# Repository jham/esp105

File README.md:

# esp105 — ESP32-C6 adapter for Mitsubishi CN105

A small board that plugs into the CN105 port of a Mitsubishi mini-split, is powered by it, and
talks to it over its serial port with an ESP32-C6 (Wi-Fi or Thread).

| Folder | Contents |
|---|---|
| [`hardware/`](hardware/) | KiCad 10 project: schematic, routed 2-layer PCB, project libraries, BOM with verified LCSC numbers, and the guide for working on it. Start with [hardware/README.md](hardware/README.md). |
| [`software/`](software/) | Firmware for the board, two choices: ESPHome over Wi-Fi for Home Assistant, or Matter over Thread for any Matter controller. Build and flashing steps are in `software/wifi/` and `software/matter/`. Start with [software/README.md](software/README.md). |

Open the board in KiCad via `hardware/cn105.kicad_pro`.

## License

The hardware design in [`hardware/`](hardware/) is licensed under the CERN Open Hardware Licence
Version 2 - Permissive; see [hardware/LICENSE](hardware/LICENSE). The firmware in
[`software/`](software/) is licensed under the Apache License 2.0; see
[software/LICENSE](software/LICENSE).

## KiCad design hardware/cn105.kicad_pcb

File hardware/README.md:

# CN105 ↔ ESP32-C6 adapter — hardware

A small board that plugs into the CN105 port of a Mitsubishi mini-split, is powered by it, and talks
to it over its 5 V serial port using an ESP32-C6 module (Wi-Fi or Thread, chosen in firmware).

**Design state:** schematic and board complete at version 0.4.0, not yet ordered (see the title
block, the `ESP105 v…` silkscreen, and [ORDER_LOG.md](ORDER_LOG.md) for what has been built; the
latest boards made are 0.3.0). What changed since 0.3.0 is under
[Changes from 0.3.0 to 0.4.0](#changes-from-030-to-040). ERC 0, DRC 0 errors, schematic parity 0. Board 41.8 × 37.6 mm, 2 layers, ESP32-C6-WROOM-1-N8 with its antenna
overhanging the top edge, Grove socket for the CN105 cable and USB-C both on the bottom edge, four M2.5 holes. The
LCSC numbers in the BOM were checked against JLCPCB's parts database. Board versions are semver;
the git tag is `v<version>` (the early tags `v0.1` and `v0.2` mean 0.1.0 and 0.2.0). A version is
tagged when it is set, whether or not it has been ordered.

## What is in this folder

| File | What it is |
|---|---|
| `cn105.kicad_pro` | The project. Double-click this to open KiCad. Contains JLCPCB-friendly design rules and two net classes (Default 0.25 mm tracks, Power 0.5 mm). |
| `cn105.kicad_sch` | The schematic. Complete, ERC 0. Its title block carries the board version and date. |
| `cn105.kicad_pcb` | The board: 41.8 × 37.6 mm, 2 layers, fully routed, GND pours on both layers. DRC 0 errors. Its title block rev/date feed the `ESP105 v${REVISION}` and `${ISSUE_DATE}` silkscreen texts on the back. |
| `cn105.kicad_sym`, `sym-lib-table` | Project symbol library: the ESP32-C6-WROOM-1 symbol (KiCad 10 does not ship one), derived from the MINI-1 symbol with the WROOM pin numbers. |
| `cn105.pretty/`, `fp-lib-table` | Project footprint library: the Grove HY2.0-4P right-angle SMD socket (drawn from the Megastar ZX-HY2.0-4PWT drawing), Espressif's official ESP32-C6-WROOM-1 footprint, and project copies of the HRO USB-C and TS-1187A switch footprints with working 3D models. The JST PA header footprints (CN105 header through 0.2.0) and the ESP32-C6-MINI-1 footprint from 0.1.0 are kept for reference. Don't delete `fp-lib-table`. |
| `cn105.3dshapes/` | 3D models not shipped with KiCad: Espressif's `ESP32-C6-WROOM-1.step` (and the 0.1.0 `ESP32-C6-MINI-1.step`) and plain-box placeholders for the Grove socket and the JST PA headers (from `tools/models.py`). The USB-C uses KiCad's GCT USB4105 model and the switches KiCad's Alps SKRK model, both near-identical parts. |
| `BOM.csv` | Human-readable parts list with LCSC numbers and the reason for each part. The JLCPCB-format BOM is generated, see below. |
| `cn105-board-3d.png` | Render of the board, regenerated with `kicad-cli pcb render` after board changes. |
| `ORDER_LOG.md` | One entry per board order: version, date, tag, fab and assembly options, what changed. |
| `tools/` | `export_jlcpcb.sh` (+ `export_jlcpcb.py`) writes the JLCPCB order files into `production/`; `set_version.py` records a board version and date in both title blocks; `jlc_stock.py` checks a JLCPCB BOM for stock and Standard-only parts; `silk_values.py` switches footprints to print their Value on the silkscreen. `gen.py`, `ksym.py`, `place.py`, `fp.py`, `models.py`, `module_fp.py` generated the original 0.1.0 starter files and **overwrite everything**; see the last section. |

## How the circuit works (read this with the schematic open)

**CN105 interface.** The board carries a 4-pin Grove (HY2.0) socket, reference CN105, and connects
to the heat pump's CN105 port with a CN105-to-Grove cable wired as on
[serin-labs.com/wiring.html](https://serin-labs.com/wiring.html): JST PAP-05V-S on the heat pump
end, Grove HY2.0-4P on ours, four conductors, the 12 V position left empty.

| Grove pin | Wire | CN105 pin | Signal | Used for |
|---|---|---|---|---|
| 1 | black | 2 | GND | Ground |
| 2 | red | 3 | 5 V | Powers the whole board |
| 3 | white | 4 | TX from the heat pump (5 V logic) | Goes through R2/R3 (10k/15k), which divides 5 V to 3.0 V, then into ESP IO7 (UART RX) |
| 4 | yellow | 5 | RX into the heat pump | Driven by U3, a 74AHCT1G125 buffer powered from 5 V, through R13 (100 Ω), so the heat pump gets a real 5 V signal. U3's input is ESP IO6 (UART TX). R6 holds that line high while the ESP is still booting so the heat pump never sees garbage. |

D4, a dual TVS diode at the socket, clamps ESD on pins 3 and 4. The cable is wired straight
through, pin for pin; the UART crossover (heat pump TX into ESP RX
and back) is built into the numbering. Grove pin 1 is at the end marked "1" on the silkscreen,
the left end when you look into the socket opening from the board edge with the latch window up.
CN105 pin 1 (12 V) stays unconnected in the cable. Verify the CN105 pinout on **your** unit with a
meter before plugging anything in.

**ESP32-C6 module.** U1 (ESP32-C6-WROOM-1-N8, 8 MB flash) with its decoupling C4 (22 µF) and C5
(100 nF) at the 3V3 pin, the EN reset circuit (R1, C1, button RESET), the BOOT button on IO9, and
three 0805 status LEDs: green PWR (R7 1k, IO23, net LED_PWR), red HEAT (R8 330 Ω, IO22, net
LED_HEAT) and blue COOL (R9 330 Ω, IO21, net LED_COOL). The resistor values give the three LEDs
similar brightness at 3.3 V (green about 50 mcd, red and blue 25–30 mcd); green and red are JLCPCB
basic parts, the blue is extended because JLCPCB stocks no basic blue 0805. UART1 is on IO6/IO7 for
the heat pump. UART0 goes to J1, a 3-pin header on the back that is not fitted (TX, RX, GND, for a
3.3 V USB-serial adapter); the console is the module's USB-Serial-JTAG over the USB-C port.
Of the strapping pins, IO9 is the BOOT button and both IO9 and IO8 carry 10k pull-ups (R12, R11) so
boot mode never depends on the weak internal pull-ups; the rest are left unconnected. The LEDs,
buttons, USB-C and module print their Value (PWR, HEAT, COOL, RESET, BOOT, USBC, ESP32-C6) on the
silkscreen instead of their reference designator.

**USB-C.** Wired for USB 2.0 only: D+/D- go straight to the C6's native USB pins (IO13/IO12, module
pads 14/13), so no USB-UART chip is needed. The receptacle's two D+ pads and two D- pads are
bridged on the board, as the USB-C spec requires. R4/R5 (5.1k) on CC1/CC2 tell a USB-C charger or
laptop we want 5 V. U4 (SRV05-4, a 4-channel TVS array with pins 1+6 and 3+4 paired on the board)
clamps ESD on D+, D- and VBUS, since the port lives in a damp metal box and gets plugged into by
hand. The VBUS pins are net `5V_USB_IN`; F1, a resettable fuse, feeds `5V_USB` from it.

**Power.** Two 5 V sources feed the `+5V` rail. USB comes in through F1 and then D1, a Schottky. The heat
pump's 5 V comes in through Q1, a P-channel MOSFET: with no USB present R10 holds its gate low and
it conducts with about 30 mV of drop; plugging in USB pulls the gate high through the `5V_USB`
line and switches it off, so USB can never back-feed the heat pump and the heat pump never drives
the USB port. Q1's body diode still lets the heat pump help out if USB sags. D1 is what keeps the
USB line separate from the rail so the gate reads "USB present". D3 (SMAJ5.0A TVS) sits across the
CN105 5 V input, C7 (100 µF) is the bulk reservoir for Wi-Fi transmit peaks, and U2 (AP2112K-3.3,
600 mA) makes 3.3 V with C2/C3 (10 µF) on its input and output. The PWR_FLAG symbols are not real
parts: they tell KiCad's checker that those nets are powered.

## Working on it in KiCad 10

**Opening.** Double-click `cn105.kicad_pro`. The project carries its own symbol and footprint
library tables, so no library setup is needed. Open the Schematic Editor or PCB Editor from the
project manager; `Home` fits the sheet or board in the window. The board sits at x=100, y=100 mm
on the sheet, so if the PCB editor looks empty press `Home`.

**Schematic.** Hover a wire and press `` ` `` (backtick) to highlight its net; `E` opens any item's
properties; `V` edits a value. **Inspect → Electrical Rules Checker → Run ERC** should report 0.
Parts carry `LCSC` and `MPN` fields; the JLCPCB export reads `LCSC`, and `MPN` is for people.

**From schematic to board.** After any schematic change press `F8` in the PCB editor (Update PCB
from Schematic) to push new parts, values and fields onto the board, then place and route what is
new. The board's `Value` field is what prints on the silkscreen for the LEDs, buttons, connectors
and module, so keep those values short.

**Board basics.** Layers tab on the right: `F.Cu`/`B.Cu` copper, `F.SilkS`/`B.SilkS` printing,
`Edge.Cuts` outline, `F.CrtYd` courtyards (the no-overlap zone around each part). White ratsnest
lines are connections not yet routed. `M` moves, `R` rotates, `E` edits, `X` routes a track, `V`
drops a via while routing, `B` refills the ground pours, `Esc` cancels. Hold `Ctrl` while moving to
ignore the grid. Don't press `F` on a part: that flips it to the back and single-sided assembly is
cheaper. `Ctrl+Shift+M` measures; `Space` sets a local origin so the status bar shows distances
from it.

**Rules already set** (File → Board Setup): 0.2 mm clearance, 0.15 mm minimum track, 0.5 mm vias
with 0.3 mm holes, matching JLCPCB's cheap 2-layer process. Net class `Power` covers `+5V`,
`+3V3`, `GND`, `5V_USB`, `5V_USB_IN` and `5V_CN105` and makes those tracks 0.5 mm
automatically; everything else is 0.25 mm.

**Antenna keep-out.** The 6 mm antenna section of the WROOM-1 (the end away from the pins) hangs
over the top edge. No copper, tracks, vias or parts under it on either layer, and Espressif asks
for no metal, including the enclosure, within about 15 mm of that end.

**Placement rules that matter.** C5 and C6 (100 nF) stay tight against the module 3V3 pin and
U3's VCC pin; C2/C3 at U2; C1, C4 and C7 are relaxed. D3 goes next to the Grove socket with a
short ground return. D1 and R10 can sit anywhere on their nets. The USB D+/D- pair runs side by
side; a via or two and a few millimetres of length mismatch are fine at USB full speed. Both
connectors are placed so their openings are flush with the bottom board edge: the Grove footprint
origin is the centre of its pad pattern (JLCPCB's reference point for the part, 3.85 mm in front
of the pin row) and the housing front is 5.45 mm from it (anchor pads stop at 5.15 mm so they keep
the 0.3 mm copper-to-edge clearance with a flush face), the USB-C origin is JLCPCB's reference point for the part (1.57 mm behind the shell centre) and
the shell front is 5.22 mm from it.

**Footprint origins must match JLCPCB's.** JLC places a part at the origin of *its* footprint
(EasyEDA's), which is the centre of the pad pattern for connectors. The CPL reports our footprint
origin, so a project footprint with its origin elsewhere is placed wrong by that offset; the Grove
socket and the USB-C both had this before 2026-11-23. Check a new footprint against
`https://easyeda.com/api/products/<LCSC>/components?version=6.5.42` (pad coordinates relative to
the origin, units of 10 mil) before trusting the placement preview.

**Checks.** `Inspect → Design Rules Checker` with schematic parity on. Expect 0 errors, 0
unconnected, and four `silk_edge_clearance` warnings where the connector and antenna outlines cross
the board edge. A "thermal relief connection incomplete" error means a GND pad is boxed in by
tracks: draw a short GND track from the pad to the nearest GND via. From the shell:

```bash
/Applications/KiCad/KiCad.app/Contents/MacOS/kicad-cli sch erc --severity-all cn105.kicad_sch
```

```bash
/Applications/KiCad/KiCad.app/Contents/MacOS/kicad-cli pcb drc --severity-all --schematic-parity --refill-zones cn105.kicad_pcb
```

**Version and date.** Both title blocks hold the board version (semver) and the date it was
set; `python3 tools/set_version.py 0.4.0` sets them with the schematic and PCB editors closed, and
the back silkscreen prints them through `${REVISION}` and `${ISSUE_DATE}`. Setting a version and
ordering boards are separate steps, each with a Claude Code skill in `.claude/skills/`:

- `/bump-version` checks whether the design files changed since the last version tag, proposes
  the next version (PATCH for part or export fixes with the schematic and copper unchanged, MINOR
  for schematic or copper changes, MAJOR on request), sets the title blocks, adds a "Changes from
  … to …" section below, runs the checks, commits and tags `v<version>`.
- `/order` builds a tagged version. If the design changed since the last tag it runs
  `/bump-version` first; if not, it orders the last tagged version again without a new number.
  It then exports the order files, waits for you to place the order, logs it in `ORDER_LOG.md`
  and pushes.

## Production files (JLCPCB)

```bash
sh tools/export_jlcpcb.sh
```

Needs KiCad in /Applications. It writes `production/` (git-ignored): `cn105-gerbers.zip` (Gerbers
for F.Cu, B.Cu, both masks, both silkscreens, F.Paste, Edge.Cuts, plus Excellon PTH/NPTH drills),
`cn105-bom-jlcpcb.csv` and `cn105-cpl-jlcpcb.csv` in JLC's column format, built from the `LCSC`
field on every part. The BOM's Comment column is the LCSC code, so JLC's matcher cannot confuse a
part with a similarly named one. Mounting holes are skipped. Through-hole parts are reported at the
centre of their pin pattern, which is what JLC's preview expects (the 0.2.0 CN105 header needed
this; the Grove socket is SMD).

```bash
python3 tools/jlc_stock.py production/cn105-bom-jlcpcb.csv
```

checks every line against JLCPCB's database and flags missing or out-of-stock parts, parts that
force Standard assembly, and which extended parts carry a loading fee.

## Firmware

Two firmwares live in [`../software/`](../software/): ESPHome over Wi-Fi in `software/wifi/` and
Matter over Thread in `software/matter/`, each with build and flashing steps. The pins both rely
on: UART TX GPIO6 and RX GPIO7, LEDs PWR GPIO23 / HEAT GPIO22 / COOL GPIO21 (high is
on), BOOT on GPIO9, console on the USB-C port.

## Bring-up checklist

1. Power from USB only. Measure +3V3 on C3: expect 3.25–3.35 V. The module should enumerate as a
   USB serial/JTAG device on the Mac (`ls /dev/cu.usb*`).
2. Flash the firmware from `software/`. The PWR LED blinks until Wi-Fi joins, then stays on.
3. Measure Grove pin 4 relative to pin 1: ~5 V (USB-powered it'll read ~4.6 V). That's UART idle.
4. Check the cable's orientation. Unplug USB, plug the Serin cable into the board's Grove socket
   with its CN105 end loose, and use the meter's continuity mode, poking a probe (or a bit of wire)
   into the cavities of the CN105 plug. Cavity 1 (the ▲ end) is empty.
   - Cavity 2 (black) beeps to the USB-C shell, which is GND.
   - Cavity 3 (red) beeps to Q1 pin 3, the lone pin on one side of the SOT-23 (the `5V_CN105`
     net), and does **not** beep to the USB-C shell.

   If black does not reach GND, the socket's pin 1 is mirrored relative to the cable; do not
   connect it to the heat pump (see the Grove note under "Things I assumed").
5. Only now plug into the heat pump. Confirm pin 3 is 5 V and pin 2 is ground **with the cable
   unplugged from the board** first, meter on the heat pump side.
6. **Do not have USB and the heat pump connected at the same time** unless the USB host is
   battery powered or you use a USB isolator. USB ties the heat pump's control ground to the
   PC's earth through this board, and the two are not guaranteed to agree. Flash on the bench,
   then install; use OTA afterwards.

## Changes from 0.3.0 to 0.4.0

0.4.0 is laid out and passes ERC, DRC and schematic parity, but it has not been ordered. The 0.3.0
boards (tag `v0.3.0`) have none of these changes, and none of them is needed for 0.3.0 to work.
The board outline, mounting holes, connectors, module position and design rules are unchanged.

### Circuit

- **R13, 100 Ω in series with U3's output** (0603, UNI-ROYAL 0603WAF1000T5E, LCSC C22775, JLCPCB
  basic). U3 pin 4 is now net `CN105_RX_BUF`, and R13 joins it to `CN105_RX_5V` at Grove pin 4.
  The 74AHCT1G125 is only rated for about 2 kV human-body ESD; R13 limits current into it from a
  static discharge, a short or a miswired cable, and costs nothing at 2400 baud.
- **D4, ESD5V0AP dual TVS on Grove pins 3 and 4** (SOT-23, ElecSuper ESD5V0AP, LCSC C5199224,
  extended). Pins 1 and 2 go to `CN105_TX_5V` and `CN105_RX_5V`, pin 3 (the common anode) to GND.
  5 V working voltage, 6 V breakdown, ±30 kV contact; the 3.3 V diodes the M5Stack NanoC6 uses
  would conduct on our 5 V signals.
- **J1, UART0 header, not fitted** (`PinHeader_1x03_P2.54mm_Vertical`, marked DNP so JLCPCB leaves
  it empty): pin 1 TXD0 (module pad 25, GPIO16, net `UART0_TX`), pin 2 RXD0 (pad 24, GPIO17,
  `UART0_RX`), pin 3 GND. With a 3.3 V USB-serial adapter it gives the ROM boot messages, and
  serial flashing with BOOT held, if firmware breaks USB-Serial-JTAG or the USB-C connector is
  damaged. It does not get around the ground warning in step 6 of the bring-up checklist, since a
  USB-serial adapter ties the grounds together just as USB-C does.
- **F1, resettable fuse on USB VBUS** (0805, BHFUSE BSMD0805-075-6V, LCSC C883110, extended; 6 V,
  0.75 A hold, 1.5 A trip). The USB-C VBUS pins and U4's VBUS clamp are now net `5V_USB_IN`
  (renamed from `USBC_5V`, and in the `Power` net class), and F1 feeds `5V_USB` from it. It
  protects the computer's USB port from a fault on this board, such as a solder bridge or a failed
  TVS or capacitor; most USB hosts already limit current, so it is the least important of the
  four. Its resistance (70–385 mΩ) adds up to about 0.1 V of drop at Wi-Fi peaks on top of D1,
  which still leaves the AP2112K enough headroom.

D4 and F1 are extended parts, each adding JLCPCB's extended-part loading fee to an order. The
firmware needs no change: no ESP pin moved.

### Layout

- **New parts.** D4 sits about 3 mm from Grove pins 3 and 4, on the connector side of R2 and R13,
  with a ground via about 1 mm from its ground pin. R13 is next to U3. F1 is on the bottom edge
  between the USB-C and Grove sockets. J1 is on the back at the right edge, with TX, RX and GND
  printed on the back silkscreen.
- **Moved to make room.** U3 and C6 moved 2.5 mm right, and R2 and R3 moved next to D4. C7 (100 µF)
  moved from beside U3 to beside U2 and Q1, where it holds up the regulator input during Wi-Fi
  peaks. Q1, D1 and R10 shifted to fit around it. C2, C3, D3, R4, R5, R6, R11 and U2 moved by about a
  millimetre or less.
- **Routing.** USB power now runs from the VBUS pins on the bottom layer to F1, and U4's VBUS
  clamp is on that side of the fuse. A bottom-layer track carries `+5V` across to U3 and C6. UART0
  runs to J1 with two vias per signal. The board went from 179 track segments and 41 vias to 216
  and 43; all power nets are still 0.5 mm.
- **Silkscreen.** Every front label is now 0.8 mm high with a 0.1 mm stroke (most were 1.0 mm with
  0.15 mm), except RESET and BOOT, which are 1.2 mm and bold.

## Things I assumed that you should double-check

- CN105 pin order (12V, GND, 5V, TX, RX) and which end is pin 1 on your unit's socket.
- The Grove socket footprint was drawn from the Megastar ZX-HY2.0-4PWT drawing. Pin 1 was taken
  to be the left end with the opening toward you and the latch window up, the JST PH convention
  the HY2.0 family copies and the numbering the Serin page uses (pin 1 = black GND). M5Stack's
  NanoC6 schematic numbers the same socket the other way (GND = pin 4), and Megastar's drawing
  numbers no pins at all, so this is unconfirmed until bring-up step 4 passes. If it is mirrored,
  the heat pump's GND lands on U3's output, its 5 V on the R2/R3 divider, its TX on the
  `5V_CN105` input and its RX on GND: the board gets no power and nothing works. The fix is a
  cable with the Grove end re-pinned in reverse order, not a new board.
- U3 must be an **AHCT** part. AHC or LVC in the same package will not translate 3.3 V → 5 V reliably.
- The heat pump's 5 V pin can supply a few hundred mA on most units. C7 (100 µF on +5V near Q1 and U2)
  is there to ride through Wi-Fi transmit peaks; if you still see resets during Wi-Fi activity,
  the supply is the suspect.
- The CN105 5 V input has a TVS (D3, SMAJ5.0A) that clamps at about 9 V. It protects against a
  mis-wired cable; it is not a substitute for checking the pinout, since a sustained 12 V would
  eventually cook it.
- It lives next to a cold coil: conformal-coat the assembled board (mask the two connectors),
  mount it above the drip path, and point the USB-C opening down or cap it.
- Thread firmware is still the open question; the hardware supports both.

## The generator scripts

`tools/gen.py`, `ksym.py`, `fp.py`, `models.py`, `module_fp.py` and `place.py` produced the
original 0.1.0 starter project (ESP32-C6-MINI-1, 48 × 30 mm, generic J1/J2 names) and are kept for
history. The current schematic and board were edited by hand from there. **Do not run them:**
`gen.py` rewrites the schematic, project file and board, and `place.py` throws away all
footprints, tracks and pours. Nothing they produce matches the current design.

## License

Copyright 2026 Jeff Hamilton.

This source describes Open Hardware and is licensed under the
[CERN Open Hardware Licence Version 2 - Permissive](https://ohwr.org/cern_ohl_p_v2.txt)
(SPDX: `CERN-OHL-P-2.0`). You may redistribute and modify this documentation and make products
using it under the terms of that licence. It is distributed WITHOUT ANY EXPRESS OR IMPLIED
WARRANTY, INCLUDING OF MERCHANTABILITY, SATISFACTORY QUALITY AND FITNESS FOR A PARTICULAR PURPOSE.
See [LICENSE](LICENSE) for the full text and conditions.

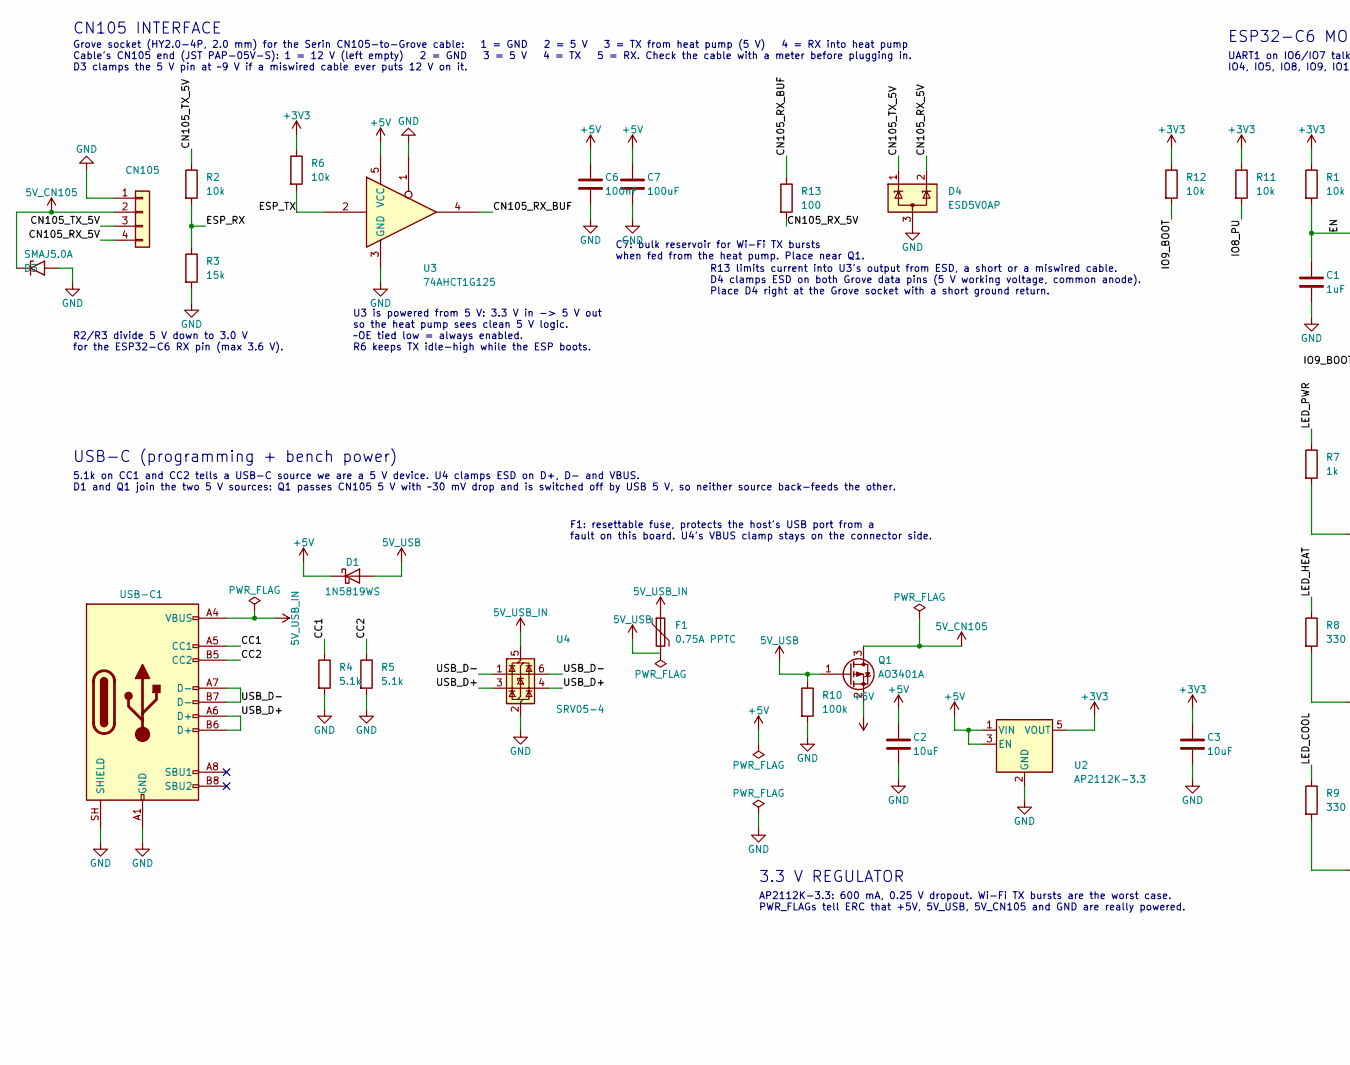
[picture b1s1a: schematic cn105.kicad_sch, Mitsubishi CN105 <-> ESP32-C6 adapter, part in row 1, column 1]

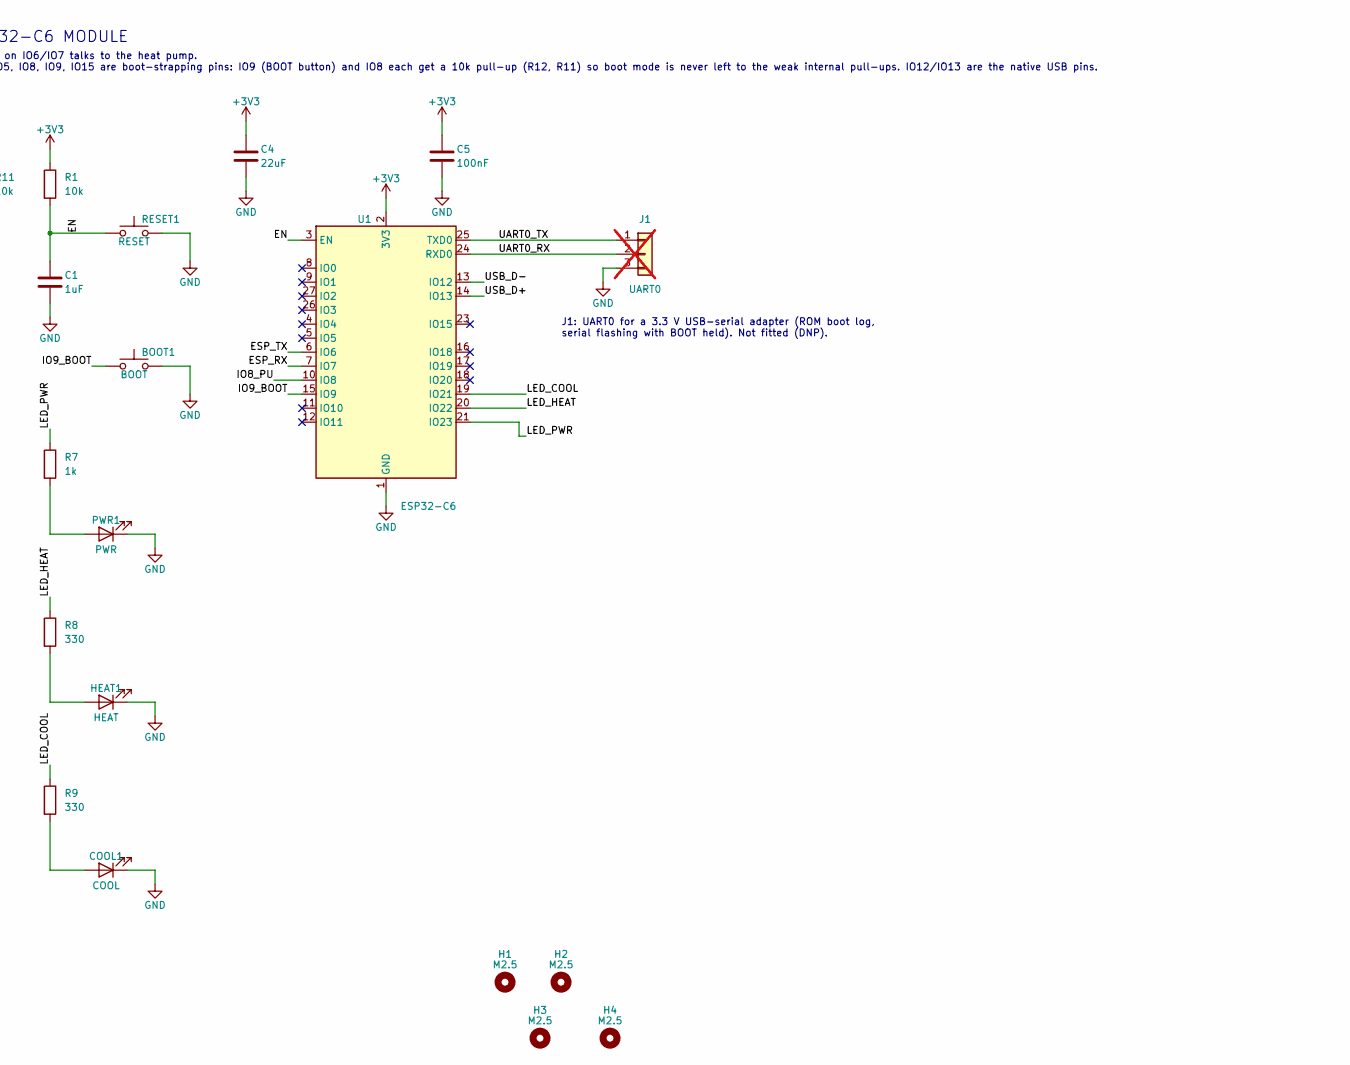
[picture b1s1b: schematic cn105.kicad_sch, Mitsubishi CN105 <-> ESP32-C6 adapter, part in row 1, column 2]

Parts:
BOOT1: BOOT; SW_Push_1P1T_XKB_TS-1187A; MPN TS-1187A-B-A-B; LCSC C318884
C1: 1uF; C_0603_1608Metric; LCSC C15849
C2, C3: 10uF; C_0603_1608Metric; LCSC C19702
C4: 22uF; C_0805_2012Metric; LCSC C45783
C5, C6: 100nF; C_0603_1608Metric; LCSC C14663
C7: 100uF; C_1206_3216Metric; LCSC C15008
CN105: CN105; Grove_HY2.0-4P_Horizontal_SMD; MPN ZX-HY2.0-4PWT; LCSC C7429571
COOL1: COOL; LED_0805_2012Metric; MPN KT-0805B; LCSC C2293
D1: 1N5819WS; D_SOD-323; LCSC C191023
D3: SMAJ5.0A; D_SMA; MPN SMAJ5.0A; LCSC C2925443
D4: ESD5V0AP; SOT-23; MPN ElecSuper ESD5V0AP; LCSC C5199224
F1: 0.75A PPTC; Fuse_0805_2012Metric; MPN BHFUSE BSMD0805-075-6V; LCSC C883110
H1, H2, H3, H4: M2.5; MountingHole_2.7mm_M2.5
HEAT1: HEAT; LED_0805_2012Metric; MPN NCD0805R1; LCSC C84256
J1: UART0; PinHeader_1x03_P2.54mm_Vertical; not fitted
PWR1: PWR; LED_0805_2012Metric; MPN KT-0805G; LCSC C2297
Q1: AO3401A; SOT-23; MPN AO3401A; LCSC C15127
R1, R2, R6, R11, R12: 10k; R_0603_1608Metric; LCSC C25804
R3: 15k; R_0603_1608Metric; LCSC C22809
R4, R5: 5.1k; R_0603_1608Metric; LCSC C23186
R7: 1k; R_0603_1608Metric; LCSC C21190
R8, R9: 330; R_0603_1608Metric; LCSC C23138
R10: 100k; R_0603_1608Metric; LCSC C25803
R13: 100; R_0603_1608Metric; MPN UNI-ROYAL 0603WAF1000T5E; LCSC C22775
RESET1: RESET; SW_Push_1P1T_XKB_TS-1187A; MPN TS-1187A-B-A-B; LCSC C318884
U1: ESP32-C6; ESP32-C6-WROOM-1; MPN ESP32-C6-WROOM-1-N8; LCSC C5366877
U2: AP2112K-3.3; SOT-23-5; MPN AP2112K-3.3TRG1; LCSC C51118
U3: 74AHCT1G125; SOT-23-5; MPN SN74AHCT1G125DBVR; LCSC C7484
U4: SRV05-4; SOT-23-6; MPN SRV05-4-P-T7; LCSC C85364
USB-C1: USBC; USB_C_Receptacle_HRO_TYPE-C-31-M-12; MPN HRO TYPE-C-31-M-12; LCSC C165948

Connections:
5V_CN105: CN105.2, D3.1 (A1), Q1.3 (D)
5V_USB: D1.2 (A), F1.2, Q1.1 (G), R10.1
5V_USB_IN: F1.1, U4.5 (VBUS), USB-C1.A4 (VBUS), USB-C1.A9 (VBUS), USB-C1.B4 (VBUS), USB-C1.B9 (VBUS)
+3V3: C3.1, C4.1, C5.1, R1.1, R6.1, R11.1, R12.1, U1.2 (3V3), U2.5 (VOUT)
+5V: C2.1, C6.1, C7.1, D1.1 (K), Q1.2 (S), U2.1 (VIN), U2.3 (EN), U3.5 (VCC)
/CC1: R4.1, USB-C1.A5 (CC1)
/CC2: R5.1, USB-C1.B5 (CC2)
/CN105_RX_5V: CN105.4, D4.2 (K), R13.2
/CN105_RX_BUF: R13.1, U3.4
/CN105_TX_5V: CN105.3, D4.1 (K), R2.1
/EN: C1.1, R1.2, RESET1.1, U1.3 (EN)
/ESP_RX: R2.2, R3.1, U1.7 (IO7)
/ESP_TX: R6.2, U1.6 (IO6), U3.2
/IO8_PU: R11.2, U1.10 (IO8)
/IO9_BOOT: BOOT1.1, R12.2, U1.15 (IO9)
/LED_COOL: R9.1, U1.19 (IO21)
/LED_HEAT: R8.1, U1.20 (IO22)
/LED_PWR: R7.1, U1.21 (IO23)
/UART0_RX: J1.2, U1.24 (RXD0)
/UART0_TX: J1.1, U1.25 (TXD0)
/USB_D+: U1.14 (IO13), U4.3 (I/O2), U4.4 (I/O2), USB-C1.A6 (D+), USB-C1.B6 (D+)
/USB_D-: U1.13 (IO12), U4.1 (I/O1), U4.6 (I/O1), USB-C1.A7 (D-), USB-C1.B7 (D-)
GND: BOOT1.2, C1.2, C2.2, C3.2, C4.2, C5.2, C6.2, C7.2, CN105.1, COOL1.1 (K), D3.2 (A2), D4.3 (A), HEAT1.1 (K), J1.3, PWR1.1 (K), R3.2, R4.2, R5.2, R10.2, RESET1.2, U1.1 (GND), U1.28 (GND), U1.29 (GND), U2.2 (GND), U3.1, U3.3 (GND), U4.2 (GND), USB-C1.A1 (GND), USB-C1.A12 (GND), USB-C1.B1 (GND), USB-C1.B12 (GND), USB-C1.SH (SHIELD)
unnamed: COOL1.2 (A), R9.2
unnamed: HEAT1.2 (A), R8.2
unnamed: PWR1.2 (A), R7.2

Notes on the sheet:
5.1k on CC1 and CC2 tells a USB-C source we are a 5 V device. U4 clamps ESD on D+, D- and VBUS. D1 and Q1 join the two 5 V sources: Q1 passes CN105 5 V with ~30 mV drop and is switched off by USB 5 V, so neither source back-feeds the other.
Grove socket (HY2.0-4P, 2.0 mm) for the Serin CN105-to-Grove cable: 1 = GND 2 = 5 V 3 = TX from heat pump (5 V) 4 = RX into heat pump Cable's CN105 end (JST PAP-05V-S): 1 = 12 V (left empty) 2 = GND 3 = 5 V 4 = TX 5 = RX. Check the cable with a meter before plugging in. D3 clamps the 5 V pin at ~9 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
R2/R3 divide 5 V down to 3.0 V for the ESP32-C6 RX pin (max 3.6 V).
USB-C (programming + bench power)
UART1 on IO6/IO7 talks to the heat pump. IO4, IO5, IO8, IO9, IO15 are boot-strapping pins: IO9 (BOOT button) and IO8 each get a 10k pull-up (R12, R11) so boot mode is never left to the weak internal pull-ups. IO12/IO13 are the native USB pins.
3.3 V REGULATOR
U3 is powered from 5 V: 3.3 V in -> 5 V out so the heat pump sees clean 5 V logic. ~OE tied low = always enabled. R6 keeps TX idle-high while the ESP boots.
C7: bulk reservoir for Wi-Fi TX bursts when fed from the heat pump. Place near Q1.
AP2112K-3.3: 600 mA, 0.25 V dropout. Wi-Fi TX bursts are the worst case. PWR_FLAGs tell ERC that +5V, 5V_USB, 5V_CN105 and GND are really powered.
ESP32-C6 MODULE
CN105 INTERFACE
R13 limits current into U3's output from ESD, a short or a miswired cable. D4 clamps ESD on both Grove data pins (5 V working voltage, common anode). Place D4 right at the Grove socket with a short ground return.
F1: resettable fuse, protects the host's USB port from a fault on this board. U4's VBUS clamp stays on the connector side.
J1: UART0 for a 3.3 V USB-serial adapter (ROM boot log, serial flashing with BOOT held). Not fitted (DNP).

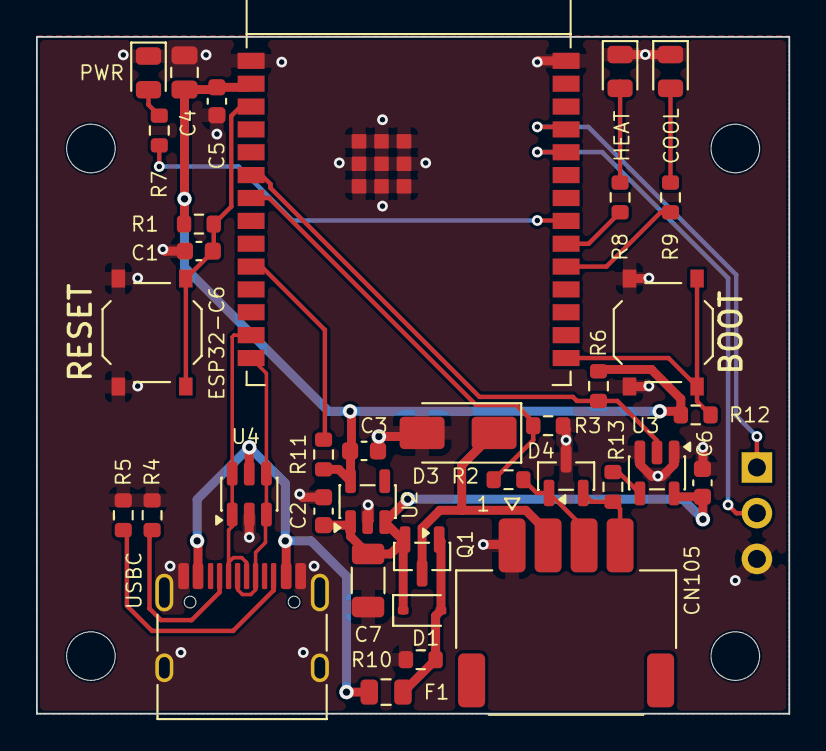
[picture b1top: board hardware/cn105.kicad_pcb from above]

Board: 2 copper layers, 41.8 x 37.6 mm, 41 parts (1 on the bottom side), 26 nets.

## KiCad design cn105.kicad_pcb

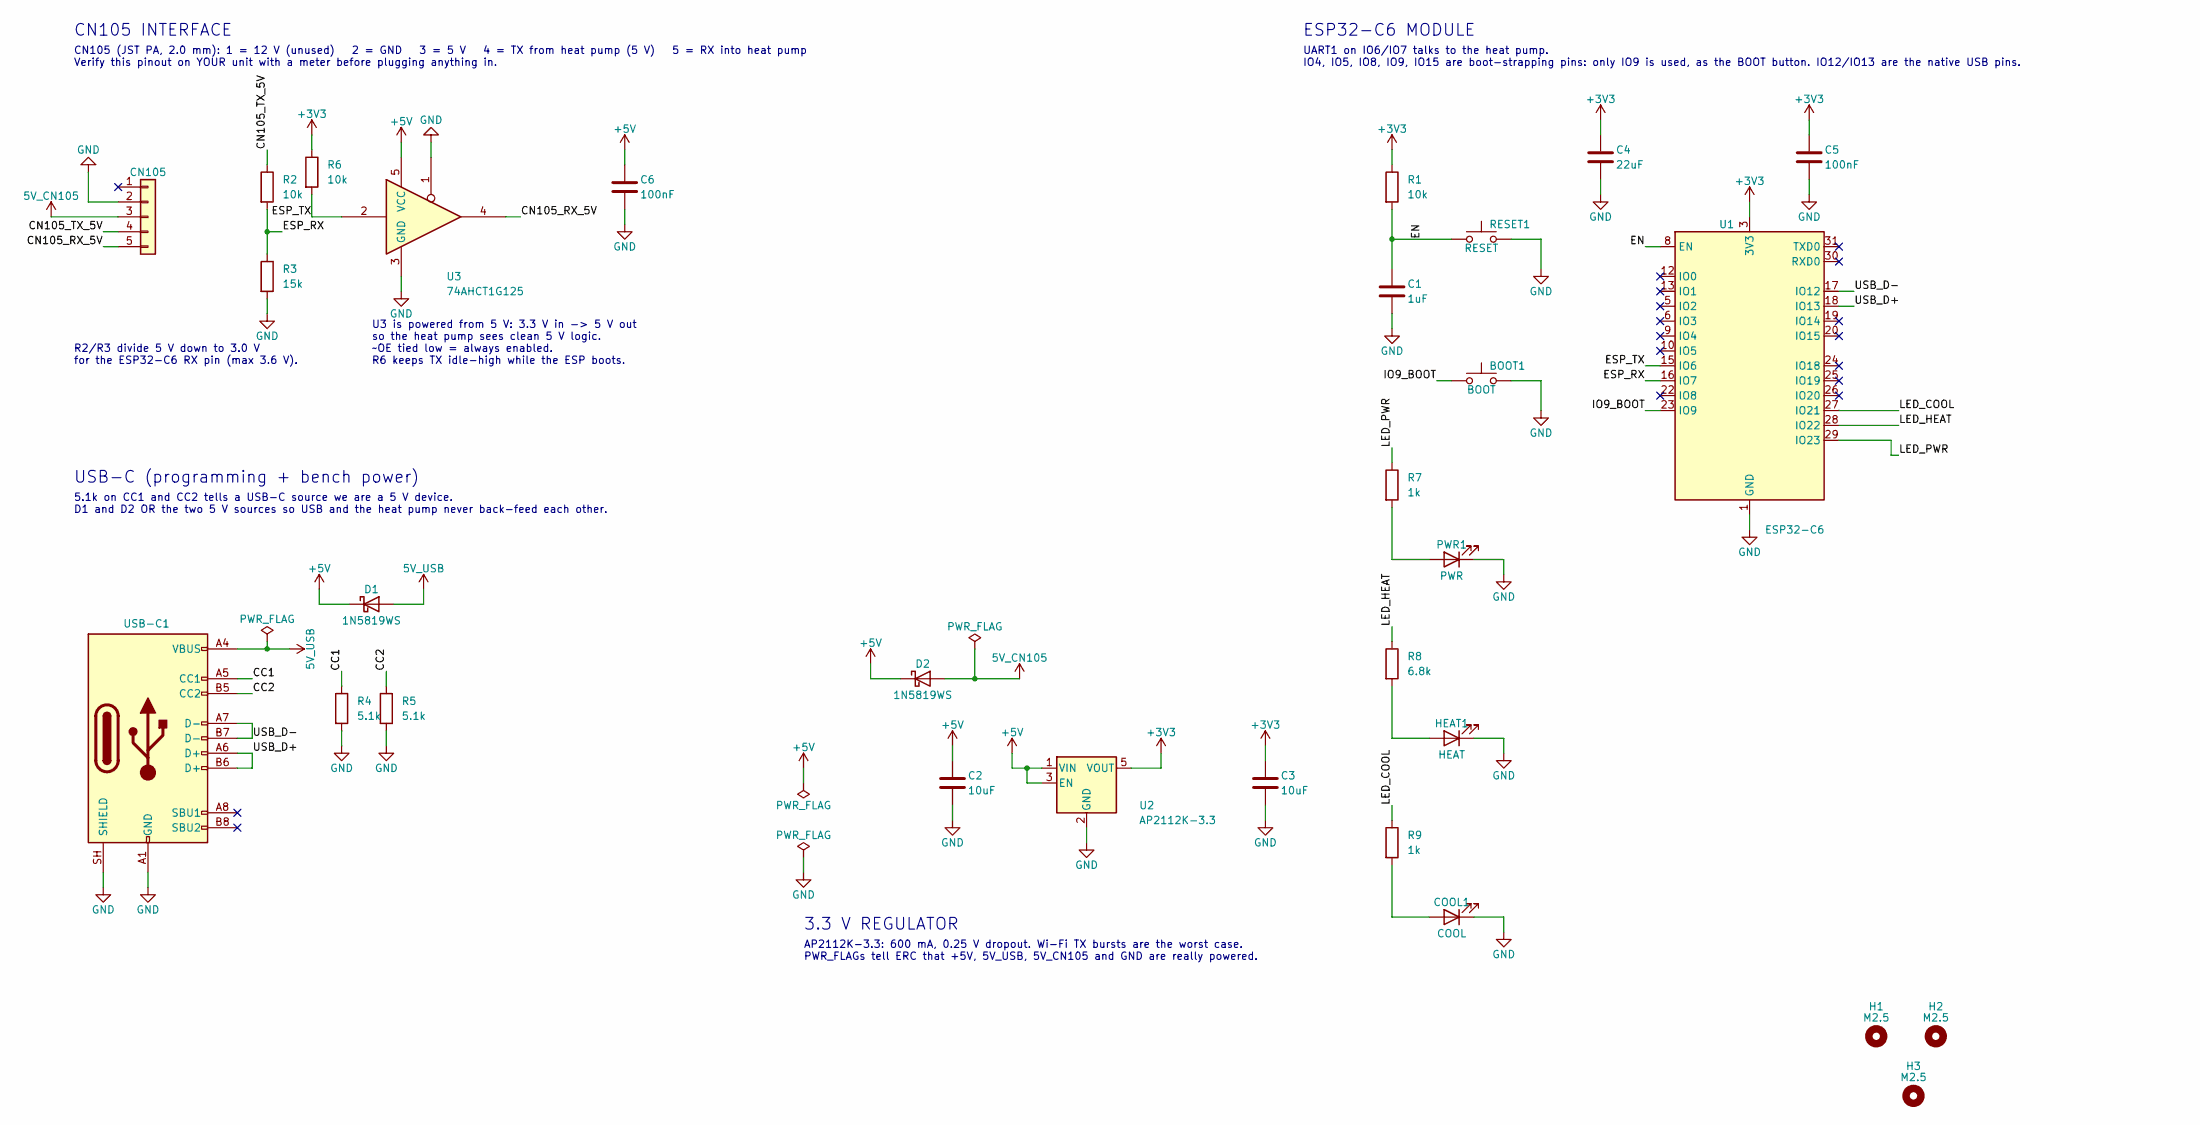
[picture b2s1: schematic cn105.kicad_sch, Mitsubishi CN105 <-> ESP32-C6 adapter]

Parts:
BOOT1: BOOT; SW_Push_1P1T_XKB_TS-1187A; LCSC C318884
C1: 1uF; C_0603_1608Metric; LCSC C5673
C2, C3: 10uF; C_0603_1608Metric; LCSC C19702
C4: 22uF; C_0805_2012Metric; LCSC C45783
C5, C6: 100nF; C_0603_1608Metric; LCSC C1591
CN105: CN105; JST_PA_S05B-PASK-2_1x05_P2.00mm_Horizontal; MPN JST S05B-PASK-2(LF)(SN); LCSC C489718
COOL1: COOL; LED_0603_1608Metric; LCSC C2288
D1, D2: 1N5819WS; D_SOD-323; LCSC C191023
H1, H2, H3: M2.5; MountingHole_2.7mm_M2.5
HEAT1: HEAT; LED_0603_1608Metric; LCSC C2286
PWR1: PWR; LED_0603_1608Metric; LCSC C12624
R1, R2, R6: 10k; R_0603_1608Metric; LCSC C25804
R3: 15k; R_0603_1608Metric; LCSC C22809
R4, R5: 5.1k; R_0603_1608Metric; LCSC C23186
R7, R9: 1k; R_0603_1608Metric; LCSC C21190
R8: 6.8k; R_0603_1608Metric; LCSC C23212
RESET1: RESET; SW_Push_1P1T_XKB_TS-1187A; LCSC C318884
U1: ESP32-C6; ESP32-C6-MINI-1; MPN ESP32-C6-MINI-1-N4; LCSC C5736265
U2: AP2112K-3.3; SOT-23-5_NoPin1Mark; MPN AP2112K-3.3TRG1; LCSC C51118
U3: 74AHCT1G125; SOT-23-5; MPN SN74AHCT1G125DBVR; LCSC C7484
USB-C1: USB-C; USB_C_Receptacle_HRO_TYPE-C-31-M-12; MPN HRO TYPE-C-31-M-12; LCSC C165948

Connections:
5V_CN105: CN105.3, D2.2 (A)
5V_USB: D1.2 (A), USB-C1.A4 (VBUS), USB-C1.A9 (VBUS), USB-C1.B4 (VBUS), USB-C1.B9 (VBUS)
+3V3: C3.1, C4.1, C5.1, R1.1, R6.1, U1.3 (3V3), U2.5 (VOUT)
+5V: C2.1, C6.1, D1.1 (K), D2.1 (K), U2.1 (VIN), U2.3 (EN), U3.5 (VCC)
/CC1: R4.1, USB-C1.A5 (CC1)
/CC2: R5.1, USB-C1.B5 (CC2)
/CN105_RX_5V: CN105.5, U3.4
/CN105_TX_5V: CN105.4, R2.1
/EN: C1.1, R1.2, RESET1.1, U1.8 (EN)
/ESP_RX: R2.2, R3.1, U1.16 (IO7)
/ESP_TX: R6.2, U1.15 (IO6), U3.2
/IO9_BOOT: BOOT1.1, U1.23 (IO9)
/LED_COOL: R9.1, U1.27 (IO21)
/LED_HEAT: R8.1, U1.28 (IO22)
/LED_PWR: R7.1, U1.29 (IO23)
/USB_D+: U1.18 (IO13), USB-C1.A6 (D+), USB-C1.B6 (D+)
/USB_D-: U1.17 (IO12), USB-C1.A7 (D-), USB-C1.B7 (D-)
GND: BOOT1.2, C1.2, C2.2, C3.2, C4.2, C5.2, C6.2, CN105.2, COOL1.1 (K), HEAT1.1 (K), PWR1.1 (K), R3.2, R4.2, R5.2, RESET1.2, U1.1 (GND), U1.2 (GND), U1.11 (GND), U1.14 (GND), U1.36 (GND), U1.37 (GND), U1.38 (GND), U1.39 (GND), U1.40 (GND), U1.41 (GND), U1.42 (GND), U1.43 (GND), U1.44 (GND), U1.45 (GND), U1.46 (GND), U1.47 (GND), U1.48 (GND), U1.49 (GND), U1.50 (GND), U1.51 (GND), U1.52 (GND), U1.53 (GND), U2.2 (GND), U3.1, U3.3 (GND), USB-C1.A1 (GND), USB-C1.A12 (GND), USB-C1.B1 (GND), USB-C1.B12 (GND), USB-C1.SH (SHIELD)
unnamed: COOL1.2 (A), R9.2
unnamed: HEAT1.2 (A), R8.2
unnamed: PWR1.2 (A), R7.2

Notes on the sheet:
5.1k on CC1 and CC2 tells a USB-C source we are a 5 V device. D1 and D2 OR the two 5 V sources so USB and the heat pump never back-feed each other.
CN105 (JST PA, 2.0 mm): 1 = 12 V (unused) 2 = GND 3 = 5 V 4 = TX from heat pump (5 V) 5 = RX into heat pump Verify this pinout on YOUR unit with a meter before plugging anything in.
R2/R3 divide 5 V down to 3.0 V for the ESP32-C6 RX pin (max 3.6 V).
USB-C (programming + bench power)
UART1 on IO6/IO7 talks to the heat pump. IO4, IO5, IO8, IO9, IO15 are boot-strapping pins: only IO9 is used, as the BOOT button. IO12/IO13 are the native USB pins.
3.3 V REGULATOR
U3 is powered from 5 V: 3.3 V in -> 5 V out so the heat pump sees clean 5 V logic. ~OE tied low = always enabled. R6 keeps TX idle-high while the ESP boots.
AP2112K-3.3: 600 mA, 0.25 V dropout. Wi-Fi TX bursts are the worst case. PWR_FLAGs tell ERC that +5V, 5V_USB, 5V_CN105 and GND are really powered.
ESP32-C6 MODULE
CN105 INTERFACE

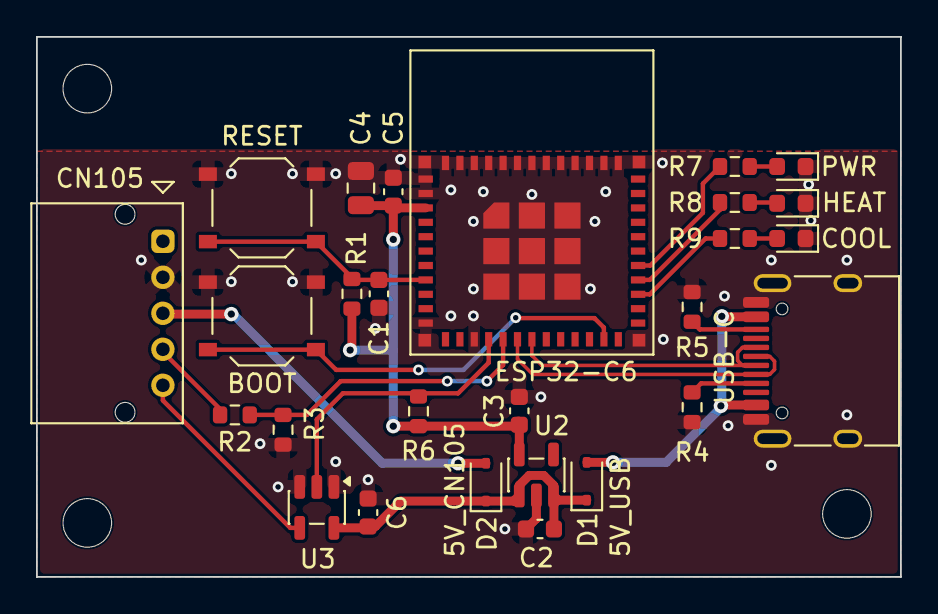
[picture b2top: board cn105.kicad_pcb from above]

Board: 2 copper layers, 48.0 x 30.0 mm, 30 parts (0 on the bottom side), 21 nets.

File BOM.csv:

Reference,Qty,Value,Package,Manufacturer part,LCSC,Notes
U1,1,ESP32-C6-MINI-1-N4,module,Espressif ESP32-C6-MINI-1-N4,C5736265,Wi-Fi 6 + 802.15.4 (Thread). Antenna end must hang over the board edge / keepout.
U2,1,AP2112K-3.3,SOT-23-5,Diodes Inc AP2112K-3.3TRG1,C51118,3.3 V LDO 600 mA
U3,1,74AHCT1G125,SOT-23-5,TI SN74AHCT1G125DBVR,C7484,5 V buffer with TTL input: 3.3 V in / 5 V out. Must be AHCT (not AHC/LVC).
CN105,1,CN105 header,JST PA 5-pin side entry,JST S05B-PASK-2(LF)(SN),C489718,2.0 mm pitch right-angle header; cable exits parallel to the board. Mates with PAP-05V-S plug on the CN105 cable. Footprint in cn105.pretty.
USB-C1,1,USB-C receptacle,HRO TYPE-C-31-M-12,HRO TYPE-C-31-M-12,C165948,16-pin USB 2.0 receptacle
RESET1 BOOT1,2,tactile switch,5.1x5.1 mm SMD,XKB TS-1187A-B-A-B,C318884,RESET and BOOT
D1 D2,2,1N5819WS,SOD-323,1N5819WS,C191023,Schottky OR-ing diodes between USB VBUS / CN105 5 V and the +5V rail
PWR1,1,PWR LED (green),0603,Hubei KENTO KT-0603G,C12624,Green power/status LED on IO23 (net LED_PWR)
HEAT1,1,HEAT LED (red),0603,Hubei KENTO KT-0603R,C2286,Red heating indicator on IO22 (net LED_HEAT)
COOL1,1,COOL LED (blue),0603,Hubei KENTO KT-0603B,C2288,Blue cooling indicator on IO21 / module pin 27 (net LED_COOL)
R1 R6,2,10k,0603,,C25804,EN pull-up / TX idle pull-up
R2,1,10k,0603,,C25804,Divider top (heat pump TX 5 V -> ESP RX)
R3,1,15k,0603,,C22809,Divider bottom. 5 V x 15/(10+15) = 3.0 V
R4 R5,2,5.1k,0603,,C23186,USB-C CC pull-downs
R7 R9,2,1k,0603,,C21190,LED series resistors (green PWR, blue COOL)
R8,1,6.8k,0603,UNI-ROYAL 0603WAF6801T5E,C23212,HEAT LED series resistor (red LED runs ~0.2 mA to match the others)
C1,1,1uF,0603,Samsung CL10A105KA8NNNC,C5673,EN reset delay (with R1) (C15849 was out of stock at LCSC on 2026-11-21)
C2 C3,2,10uF,0603,,C19702,LDO input / output
C4,1,22uF,0805,,C45783,Module bulk decoupling (close to U1 pin 3)
C5 C6,2,100nF,0603,Samsung CL10B104KB8NNNC,C1591,Module and buffer decoupling (C14663 was out of stock at LCSC on 2026-11-21)
H1 H2 H3,3,M2.5 mounting hole,2.7 mm,,,No part to buy
